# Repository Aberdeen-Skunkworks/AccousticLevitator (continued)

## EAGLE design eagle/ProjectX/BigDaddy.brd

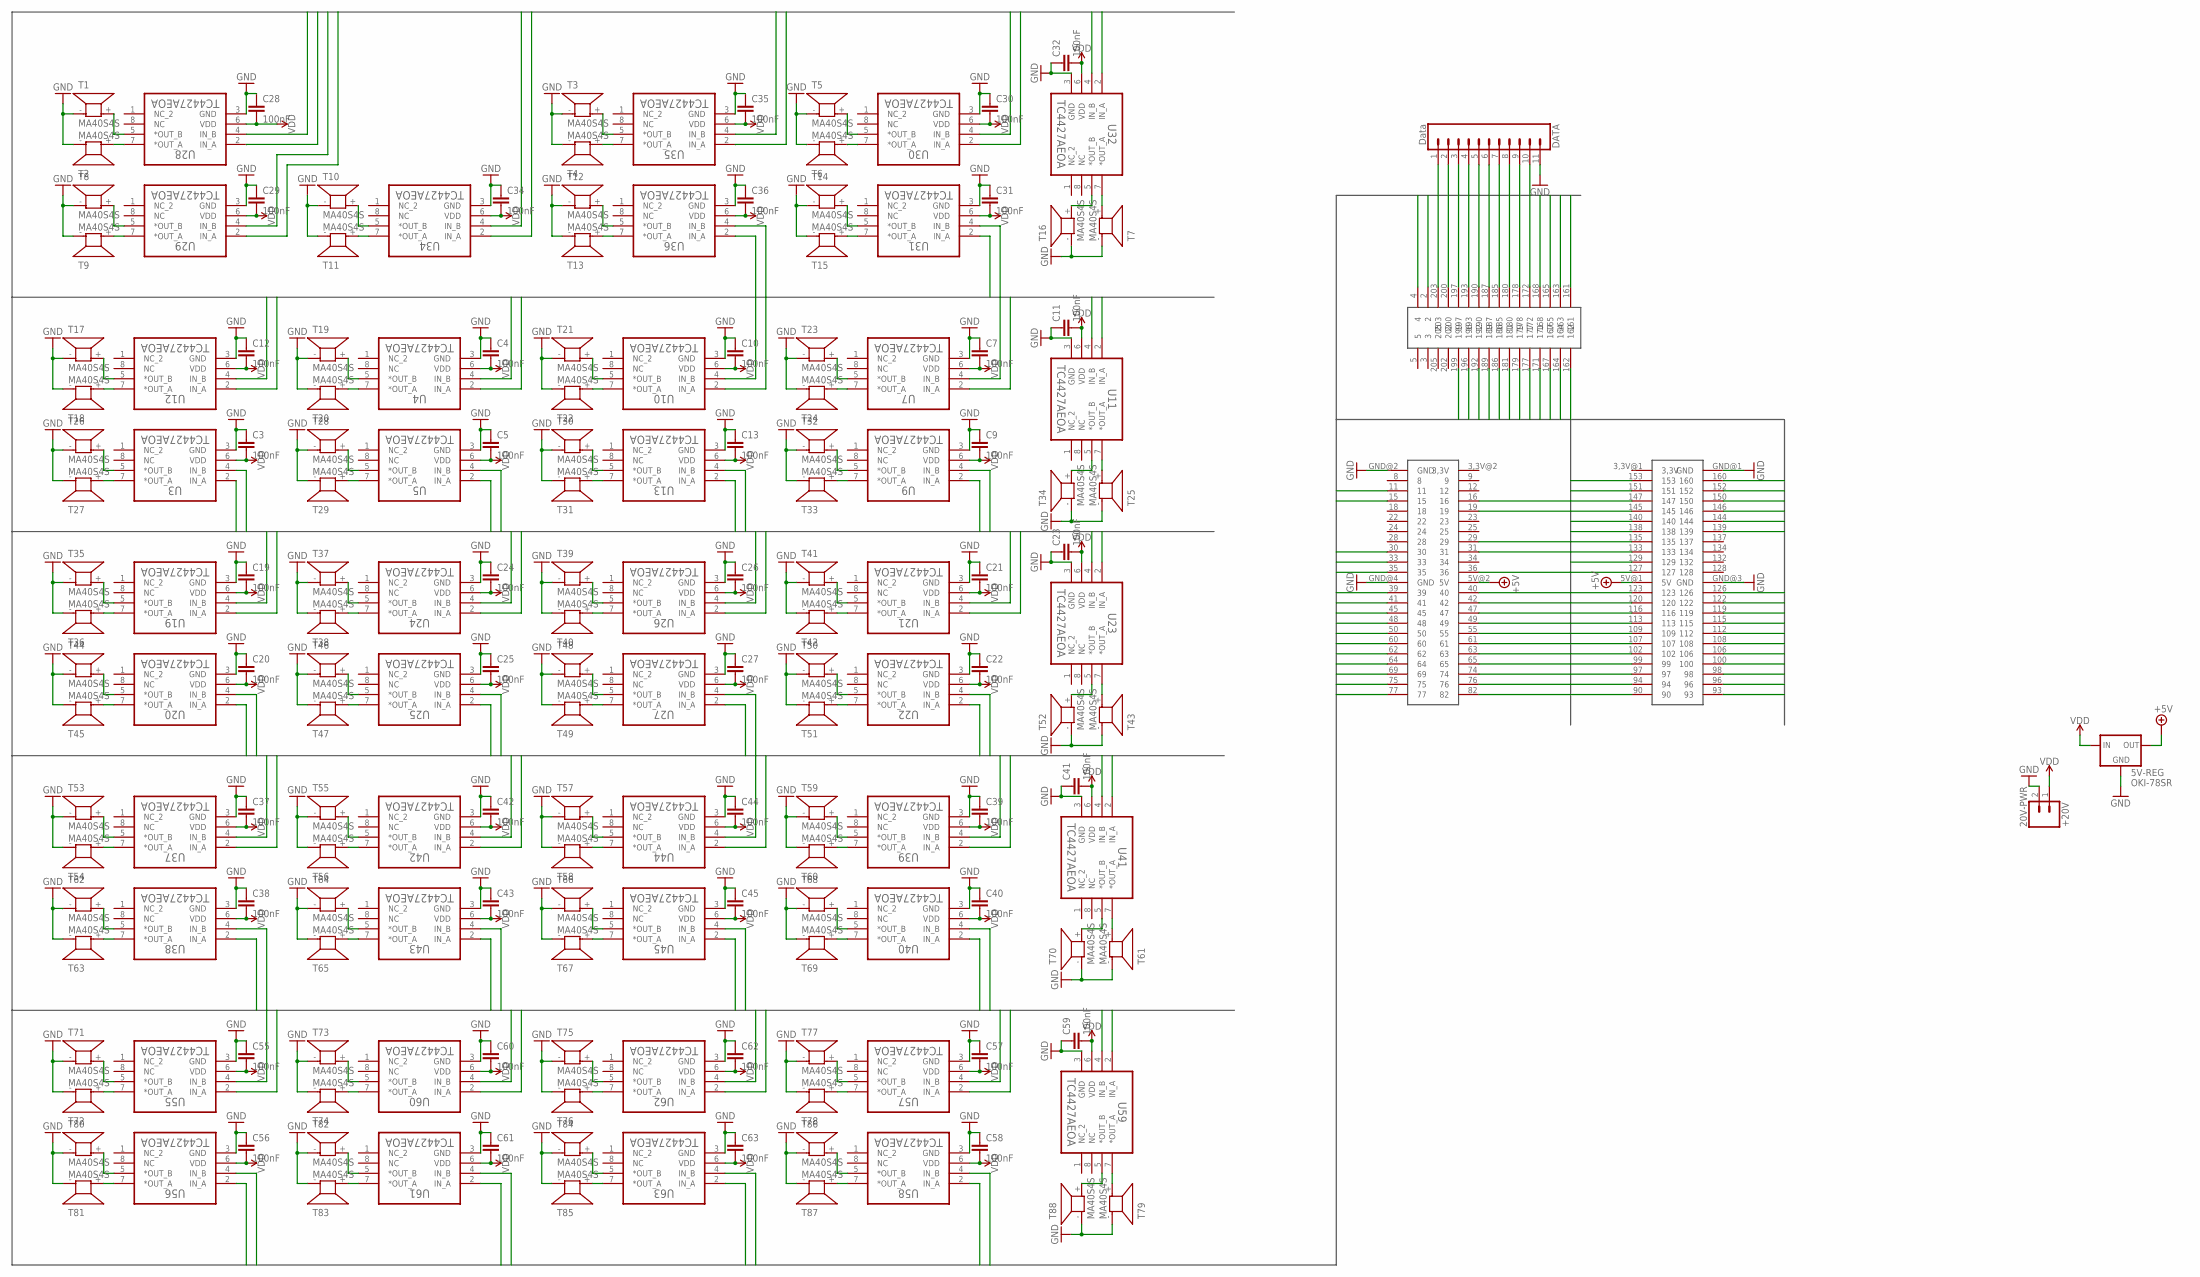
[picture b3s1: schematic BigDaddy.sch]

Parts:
5V-REG: OKI-78SR; OKI-78SR-HORIZ
20V-PWR: +20V; 1X02_LOCK_LONGPADS
C3, C4, C5, C7, C9, C10, C11, C12, C13, C19, C20, C21, C22, C23, C24, C25, C26, C27, C28, C29, C30, C31, C32, C34, C35, C36, C37, C38, C39, C40, C41, C42, C43, C44, C45, C55, C56, C57, C58, C59, C60, C61, C62, C63: 100nF; C0805
DATA: Data; 1X11
DIP1: CORE3S500ESMT; CORE3S500E-SMT
T1, T2, T3, T4, T5, T6, T7, T8, T9, T10, T11, T12, T13, T14, T15, T16, T17, T18, T19, T20, T21, T22, T23, T24, T25, T26, T27, T28, T29, T30, T31, T32, T33, T34, T35, T36, T37, T38, T39, T40, T41, T42, T43, T44, T45, T46, T47, T48, T49, T50, T51, T52, T53, T54, T55, T56, T57, T58, T59, T60, T61, T62, T63, T64, T65, T66, T67, T68, T69, T70, T71, T72, T73, T74, T75, T76, T77, T78, T79, T80, T81, T82, T83, T84, T85, T86, T87, T88: MA40S4S; MA40
U3, U4, U5, U7, U9, U10, U11, U12, U13, U19, U20, U21, U22, U23, U24, U25, U26, U27, U28, U29, U30, U31, U32, U34, U35, U36, U37, U38, U39, U40, U41, U42, U43, U44, U45, U55, U56, U57, U58, U59, U60, U61, U62, U63: TC4427AEOA; SOIC127P600X175-8N

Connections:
1: DIP1.2, U28.4 (IN_B)
2: DIP1.4, U28.2 (IN_A)
3: DIP1.165, U35.4 (IN_B)
4: DIP1.168, U35.2 (IN_A)
5: DIP1.163, U30.4 (IN_B)
6: DIP1.161, U30.2 (IN_A)
7: DIP1.162, U32.2 (IN_A)
8: DIP1.196, U29.4 (IN_B)
9: DIP1.199, U29.2 (IN_A)
10: DIP1.192, U34.4 (IN_B)
11: DIP1.189, U34.2 (IN_A)
12: DIP1.177, U36.4 (IN_B)
13: DIP1.179, U36.2 (IN_A)
14: DIP1.171, U31.4 (IN_B)
15: DIP1.167, U31.2 (IN_A)
16: DIP1.164, U32.4 (IN_B)
17: DIP1.11, U12.4 (IN_B)
18: DIP1.15, U12.2 (IN_A)
19: DIP1.19, U4.4 (IN_B)
20: DIP1.16, U4.2 (IN_A)
21: DIP1.186, U10.4 (IN_B)
22: DIP1.181, U10.2 (IN_A)
23: DIP1.152, U7.4 (IN_B)
24: DIP1.160, U7.2 (IN_A)
25: DIP1.150, U11.2 (IN_A)
26: DIP1.30, U3.4 (IN_B)
27: DIP1.33, U3.2 (IN_A)
28: DIP1.31, U5.4 (IN_B)
29: DIP1.29, U5.2 (IN_A)
30: DIP1.153, U13.4 (IN_B)
31: DIP1.151, U13.2 (IN_A)
32: DIP1.139, U9.4 (IN_B)
33: DIP1.144, U9.2 (IN_A)
34: DIP1.146, U11.4 (IN_B)
35: DIP1.35, U19.4 (IN_B)
36: DIP1.39, U19.2 (IN_A)
37: DIP1.40, U24.4 (IN_B)
38: DIP1.36, U24.2 (IN_A)
39: DIP1.147, U26.4 (IN_B)
40: DIP1.145, U26.2 (IN_A)
41: DIP1.122, U21.4 (IN_B)
42: DIP1.126, U21.2 (IN_A)
43: DIP1.119, U23.2 (IN_A)
44: DIP1.41, U20.4 (IN_B)
45: DIP1.45, U20.2 (IN_A)
46: DIP1.47, U25.4 (IN_B)
47: DIP1.42, U25.2 (IN_A)
48: DIP1.140, U27.4 (IN_B)
49: DIP1.138, U27.2 (IN_A)
50: DIP1.108, U22.4 (IN_B)
51: DIP1.112, U22.2 (IN_A)
52: DIP1.115, U23.4 (IN_B)
53: DIP1.48, U37.4 (IN_B)
54: DIP1.50, U37.2 (IN_A)
55: DIP1.55, U42.4 (IN_B)
56: DIP1.49, U42.2 (IN_A)
57: DIP1.135, U44.4 (IN_B)
58: DIP1.133, U44.2 (IN_A)
59: DIP1.100, U39.4 (IN_B)
60: DIP1.106, U39.2 (IN_A)
61: DIP1.98, U41.2 (IN_A)
62: DIP1.77, U38.4 (IN_B)
63: DIP1.75, U38.2 (IN_A)
64: DIP1.63, U43.4 (IN_B)
65: DIP1.61, U43.2 (IN_A)
66: DIP1.129, U45.4 (IN_B)
67: DIP1.127, U45.2 (IN_A)
68: DIP1.109, U40.4 (IN_B)
69: DIP1.93, U40.2 (IN_A)
70: DIP1.96, U41.4 (IN_B)
71: DIP1.69, U55.4 (IN_B)
72: DIP1.64, U55.2 (IN_A)
73: DIP1.74, U60.4 (IN_B)
74: DIP1.65, U60.2 (IN_A)
75: DIP1.123, U62.4 (IN_B)
76: DIP1.120, U62.2 (IN_A)
77: DIP1.102, U57.4 (IN_B)
78: DIP1.107, U57.2 (IN_A)
79: DIP1.99, U59.2 (IN_A)
80: DIP1.62, U56.4 (IN_B)
81: DIP1.60, U56.2 (IN_A)
82: DIP1.82, U61.4 (IN_B)
83: DIP1.76, U61.2 (IN_A)
84: DIP1.116, U63.4 (IN_B)
85: DIP1.113, U63.2 (IN_A)
86: DIP1.94, U58.4 (IN_B)
87: DIP1.90, U58.2 (IN_A)
88: DIP1.97, U59.4 (IN_B)
+5V: 5V-REG.OUT, DIP1.5V@1 (5V), DIP1.5V@2 (5V)
GND: 5V-REG.GND, 20V-PWR.2, C3.1, C4.1, C5.1, C7.1, C9.1, C10.1, C11.1, C12.1, C13.1, C19.1, C20.1, C21.1, C22.1, C23.1, C24.1, C25.1, C26.1, C27.1, C28.1, C29.1, C30.1, C31.1, C32.1, C34.1, C35.1, C36.1, C37.1, C38.1, C39.1, C40.1, C41.1, C42.1, C43.1, C44.1, C45.1, C55.1, C56.1, C57.1, C58.1, C59.1, C60.1, C61.1, C62.1, C63.1, DATA.11, DIP1.GND@1 (GND), DIP1.GND@2 (GND), DIP1.GND@3 (GND), DIP1.GND@4 (GND), T1.- (1), T2.- (1), T3.- (1), T4.- (1), T5.- (1), T6.- (1), T7.- (1), T8.- (1), T9.- (1), T10.- (1), T11.- (1), T12.- (1), T13.- (1), T14.- (1), T15.- (1), T16.- (1), T17.- (1), T18.- (1), T19.- (1), T20.- (1), T21.- (1), T22.- (1), T23.- (1), T24.- (1), T25.- (1), T26.- (1), T27.- (1), T28.- (1), T29.- (1), T30.- (1), T31.- (1), T32.- (1), T33.- (1), T34.- (1), T35.- (1), T36.- (1), T37.- (1), T38.- (1), T39.- (1), T40.- (1), T41.- (1), T42.- (1), T43.- (1), T44.- (1), T45.- (1), T46.- (1), T47.- (1), T48.- (1), T49.- (1), T50.- (1), T51.- (1), T52.- (1), T53.- (1), T54.- (1), T55.- (1), T56.- (1), T57.- (1), T58.- (1), T59.- (1), T60.- (1), T61.- (1), T62.- (1), T63.- (1), T64.- (1), T65.- (1), T66.- (1), T67.- (1), T68.- (1), T69.- (1), T70.- (1), T71.- (1), T72.- (1), T73.- (1), T74.- (1), T75.- (1), T76.- (1), T77.- (1), T78.- (1), T79.- (1), T80.- (1), T81.- (1), T82.- (1), T83.- (1), T84.- (1), T85.- (1), T86.- (1), T87.- (1), T88.- (1), U3.3 (GND), U4.3 (GND), U5.3 (GND), U7.3 (GND), U9.3 (GND), U10.3 (GND), U11.3 (GND), U12.3 (GND), U13.3 (GND), U19.3 (GND), U20.3 (GND), U21.3 (GND), U22.3 (GND), U23.3 (GND), U24.3 (GND), U25.3 (GND), U26.3 (GND), U27.3 (GND), U28.3 (GND), U29.3 (GND), U30.3 (GND), U31.3 (GND), U32.3 (GND), U34.3 (GND), U35.3 (GND), U36.3 (GND), U37.3 (GND), U38.3 (GND), U39.3 (GND), U40.3 (GND), U41.3 (GND), U42.3 (GND), U43.3 (GND), U44.3 (GND), U45.3 (GND), U55.3 (GND), U56.3 (GND), U57.3 (GND), U58.3 (GND), U59.3 (GND), U60.3 (GND), U61.3 (GND), U62.3 (GND), U63.3 (GND)
unnamed: DATA.1, DIP1.203
unnamed: DATA.2, DIP1.200
unnamed: DATA.3, DIP1.197
unnamed: DATA.4, DIP1.193
unnamed: T27.+ (2), U3.7 (*OUT_A)
unnamed: T26.+ (2), U3.5 (*OUT_B)
unnamed: T20.+ (2), U4.7 (*OUT_A)
unnamed: T19.+ (2), U4.5 (*OUT_B)
unnamed: T29.+ (2), U5.7 (*OUT_A)
unnamed: T28.+ (2), U5.5 (*OUT_B)
unnamed: DATA.5, DIP1.190
unnamed: DATA.6, DIP1.187
unnamed: T24.+ (2), U7.7 (*OUT_A)
unnamed: T23.+ (2), U7.5 (*OUT_B)
unnamed: DATA.7, DIP1.185
unnamed: DATA.8, DIP1.180
unnamed: T33.+ (2), U9.7 (*OUT_A)
unnamed: T32.+ (2), U9.5 (*OUT_B)
unnamed: T22.+ (2), U10.7 (*OUT_A)
unnamed: T21.+ (2), U10.5 (*OUT_B)
unnamed: T25.+ (2), U11.7 (*OUT_A)
unnamed: T34.+ (2), U11.5 (*OUT_B)
unnamed: T18.+ (2), U12.7 (*OUT_A)
unnamed: T17.+ (2), U12.5 (*OUT_B)
unnamed: T31.+ (2), U13.7 (*OUT_A)
unnamed: T30.+ (2), U13.5 (*OUT_B)
unnamed: DATA.9, DIP1.178
unnamed: DATA.10, DIP1.172
unnamed: T36.+ (2), U19.7 (*OUT_A)
unnamed: T35.+ (2), U19.5 (*OUT_B)
unnamed: T45.+ (2), U20.7 (*OUT_A)
unnamed: T44.+ (2), U20.5 (*OUT_B)
unnamed: T42.+ (2), U21.7 (*OUT_A)
unnamed: T41.+ (2), U21.5 (*OUT_B)
unnamed: T51.+ (2), U22.7 (*OUT_A)
unnamed: T50.+ (2), U22.5 (*OUT_B)
unnamed: T43.+ (2), U23.7 (*OUT_A)
unnamed: T52.+ (2), U23.5 (*OUT_B)
unnamed: T38.+ (2), U24.7 (*OUT_A)
unnamed: T37.+ (2), U24.5 (*OUT_B)
unnamed: T47.+ (2), U25.7 (*OUT_A)
unnamed: T46.+ (2), U25.5 (*OUT_B)
unnamed: T40.+ (2), U26.7 (*OUT_A)
unnamed: T39.+ (2), U26.5 (*OUT_B)
unnamed: T49.+ (2), U27.7 (*OUT_A)
unnamed: T48.+ (2), U27.5 (*OUT_B)
unnamed: T2.+ (2), U28.7 (*OUT_A)
unnamed: T1.+ (2), U28.5 (*OUT_B)
unnamed: T9.+ (2), U29.7 (*OUT_A)
unnamed: T8.+ (2), U29.5 (*OUT_B)
unnamed: T6.+ (2), U30.7 (*OUT_A)
unnamed: T5.+ (2), U30.5 (*OUT_B)
unnamed: T15.+ (2), U31.7 (*OUT_A)
unnamed: T14.+ (2), U31.5 (*OUT_B)
unnamed: T7.+ (2), U32.7 (*OUT_A)
unnamed: T16.+ (2), U32.5 (*OUT_B)
unnamed: T11.+ (2), U34.7 (*OUT_A)
unnamed: T10.+ (2), U34.5 (*OUT_B)
unnamed: T4.+ (2), U35.7 (*OUT_A)
unnamed: T3.+ (2), U35.5 (*OUT_B)
unnamed: T13.+ (2), U36.7 (*OUT_A)
unnamed: T12.+ (2), U36.5 (*OUT_B)
unnamed: T54.+ (2), U37.7 (*OUT_A)
unnamed: T53.+ (2), U37.5 (*OUT_B)
unnamed: T63.+ (2), U38.7 (*OUT_A)
unnamed: T62.+ (2), U38.5 (*OUT_B)
unnamed: T60.+ (2), U39.7 (*OUT_A)
unnamed: T59.+ (2), U39.5 (*OUT_B)
unnamed: T69.+ (2), U40.7 (*OUT_A)
unnamed: T68.+ (2), U40.5 (*OUT_B)
unnamed: T61.+ (2), U41.7 (*OUT_A)
unnamed: T70.+ (2), U41.5 (*OUT_B)
unnamed: T56.+ (2), U42.7 (*OUT_A)
unnamed: T55.+ (2), U42.5 (*OUT_B)
unnamed: T65.+ (2), U43.7 (*OUT_A)
unnamed: T64.+ (2), U43.5 (*OUT_B)
unnamed: T58.+ (2), U44.7 (*OUT_A)
unnamed: T57.+ (2), U44.5 (*OUT_B)
unnamed: T67.+ (2), U45.7 (*OUT_A)
unnamed: T66.+ (2), U45.5 (*OUT_B)
unnamed: T72.+ (2), U55.7 (*OUT_A)
unnamed: T71.+ (2), U55.5 (*OUT_B)
unnamed: T81.+ (2), U56.7 (*OUT_A)
unnamed: T80.+ (2), U56.5 (*OUT_B)
unnamed: T78.+ (2), U57.7 (*OUT_A)
unnamed: T77.+ (2), U57.5 (*OUT_B)
unnamed: T87.+ (2), U58.7 (*OUT_A)
unnamed: T86.+ (2), U58.5 (*OUT_B)
unnamed: T79.+ (2), U59.7 (*OUT_A)
unnamed: T88.+ (2), U59.5 (*OUT_B)
unnamed: T74.+ (2), U60.7 (*OUT_A)
unnamed: T73.+ (2), U60.5 (*OUT_B)
unnamed: T83.+ (2), U61.7 (*OUT_A)
unnamed: T82.+ (2), U61.5 (*OUT_B)
unnamed: T76.+ (2), U62.7 (*OUT_A)
unnamed: T75.+ (2), U62.5 (*OUT_B)
unnamed: T85.+ (2), U63.7 (*OUT_A)
unnamed: T84.+ (2), U63.5 (*OUT_B)
VDD: 5V-REG.IN, 20V-PWR.1, C3.2, C4.2, C5.2, C7.2, C9.2, C10.2, C11.2, C12.2, C13.2, C19.2, C20.2, C21.2, C22.2, C23.2, C24.2, C25.2, C26.2, C27.2, C28.2, C29.2, C30.2, C31.2, C32.2, C34.2, C35.2, C36.2, C37.2, C38.2, C39.2, C40.2, C41.2, C42.2, C43.2, C44.2, C45.2, C55.2, C56.2, C57.2, C58.2, C59.2, C60.2, C61.2, C62.2, C63.2, U3.6 (VDD), U4.6 (VDD), U5.6 (VDD), U7.6 (VDD), U9.6 (VDD), U10.6 (VDD), U11.6 (VDD), U12.6 (VDD), U13.6 (VDD), U19.6 (VDD), U20.6 (VDD), U21.6 (VDD), U22.6 (VDD), U23.6 (VDD), U24.6 (VDD), U25.6 (VDD), U26.6 (VDD), U27.6 (VDD), U28.6 (VDD), U29.6 (VDD), U30.6 (VDD), U31.6 (VDD), U32.6 (VDD), U34.6 (VDD), U35.6 (VDD), U36.6 (VDD), U37.6 (VDD), U38.6 (VDD), U39.6 (VDD), U40.6 (VDD), U41.6 (VDD), U42.6 (VDD), U43.6 (VDD), U44.6 (VDD), U45.6 (VDD), U55.6 (VDD), U56.6 (VDD), U57.6 (VDD), U58.6 (VDD), U59.6 (VDD), U60.6 (VDD), U61.6 (VDD), U62.6 (VDD), U63.6 (VDD)

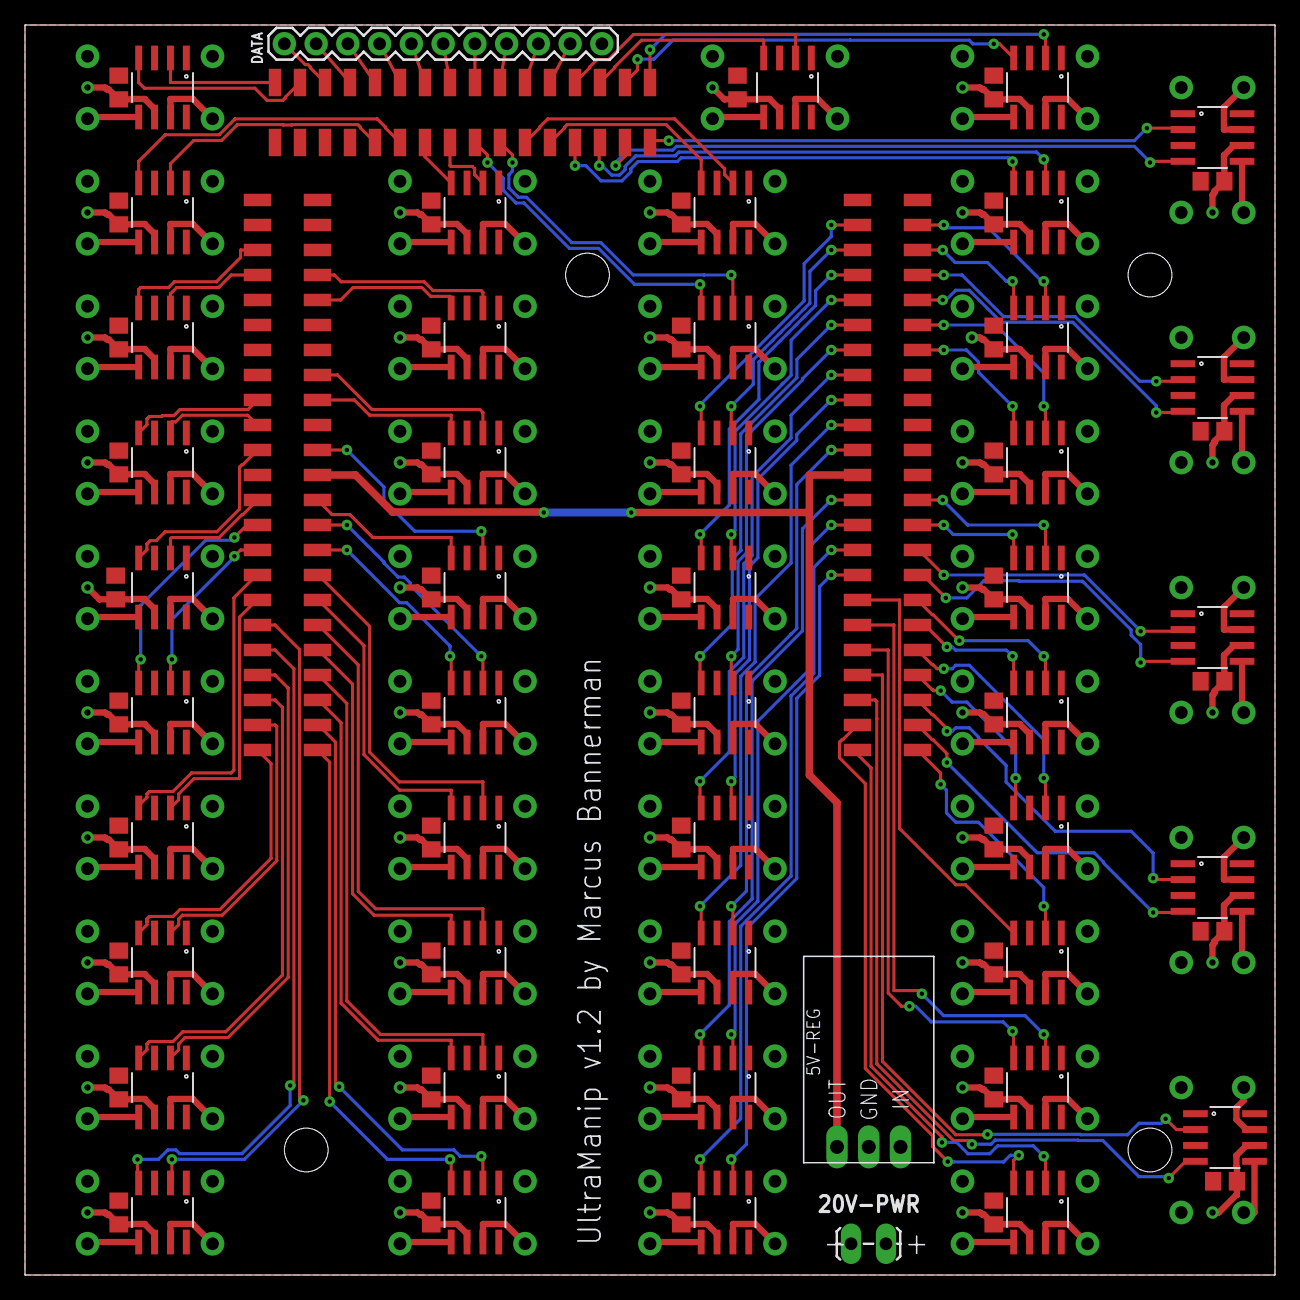
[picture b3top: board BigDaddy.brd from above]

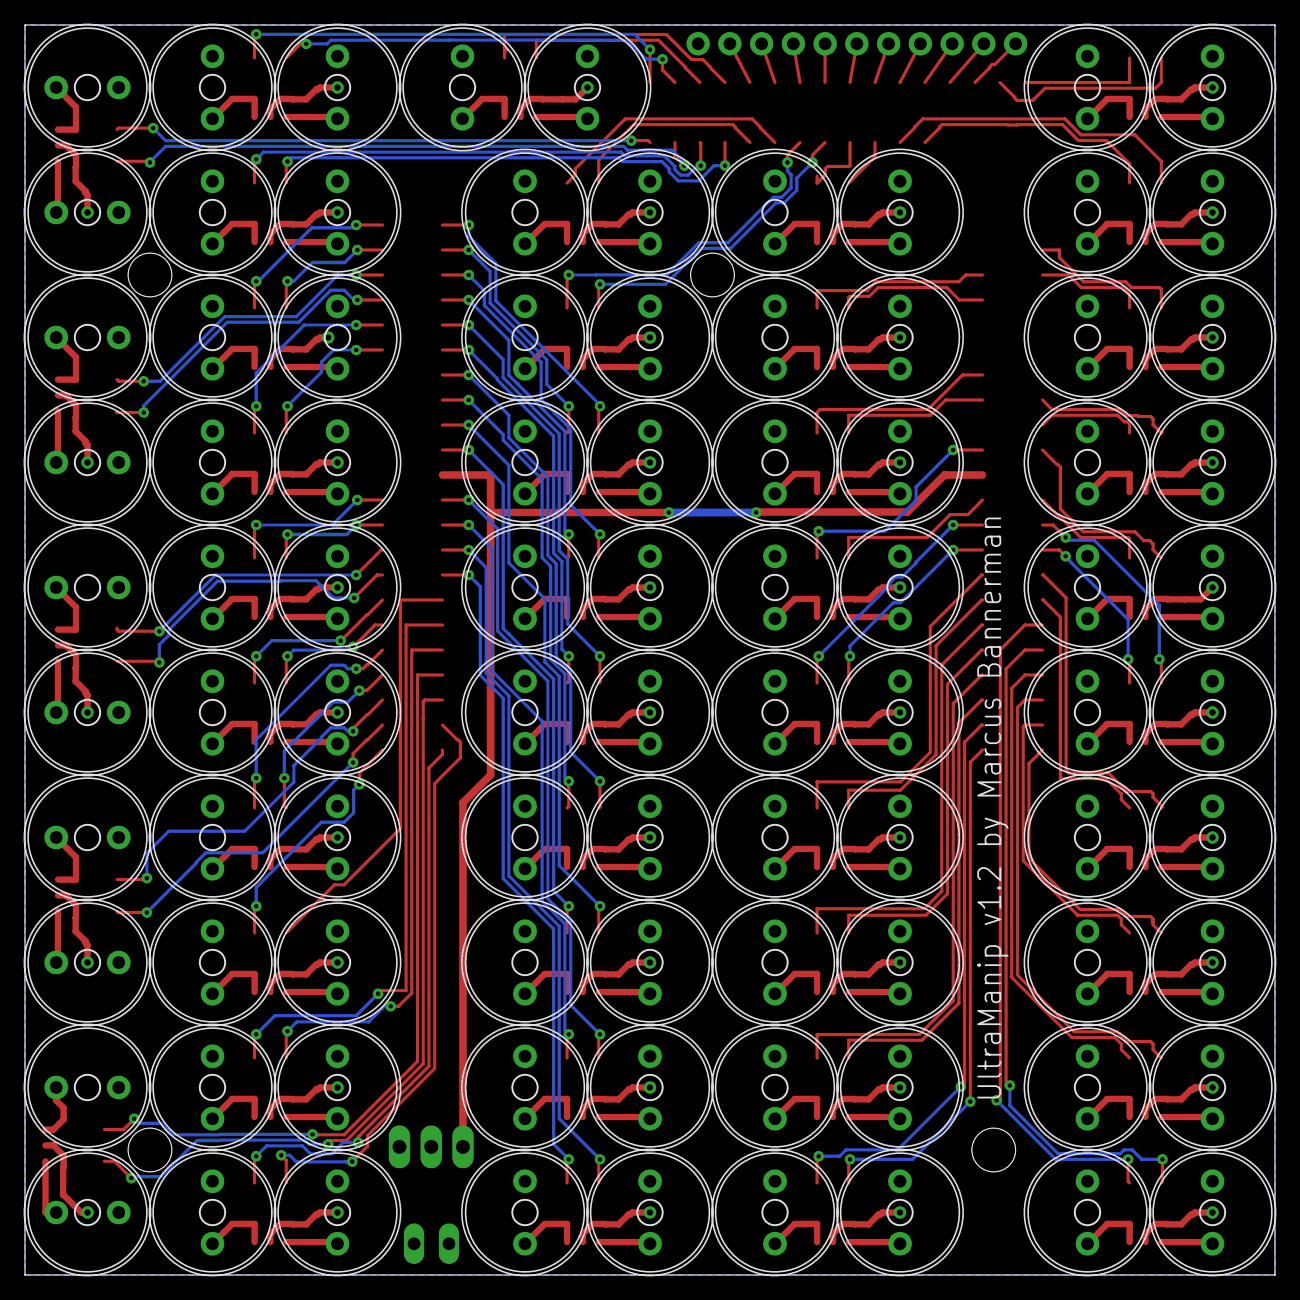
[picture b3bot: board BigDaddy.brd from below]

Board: 2 copper layers, 100.0 x 100.0 mm, 180 parts (88 on the bottom side), 189 nets.

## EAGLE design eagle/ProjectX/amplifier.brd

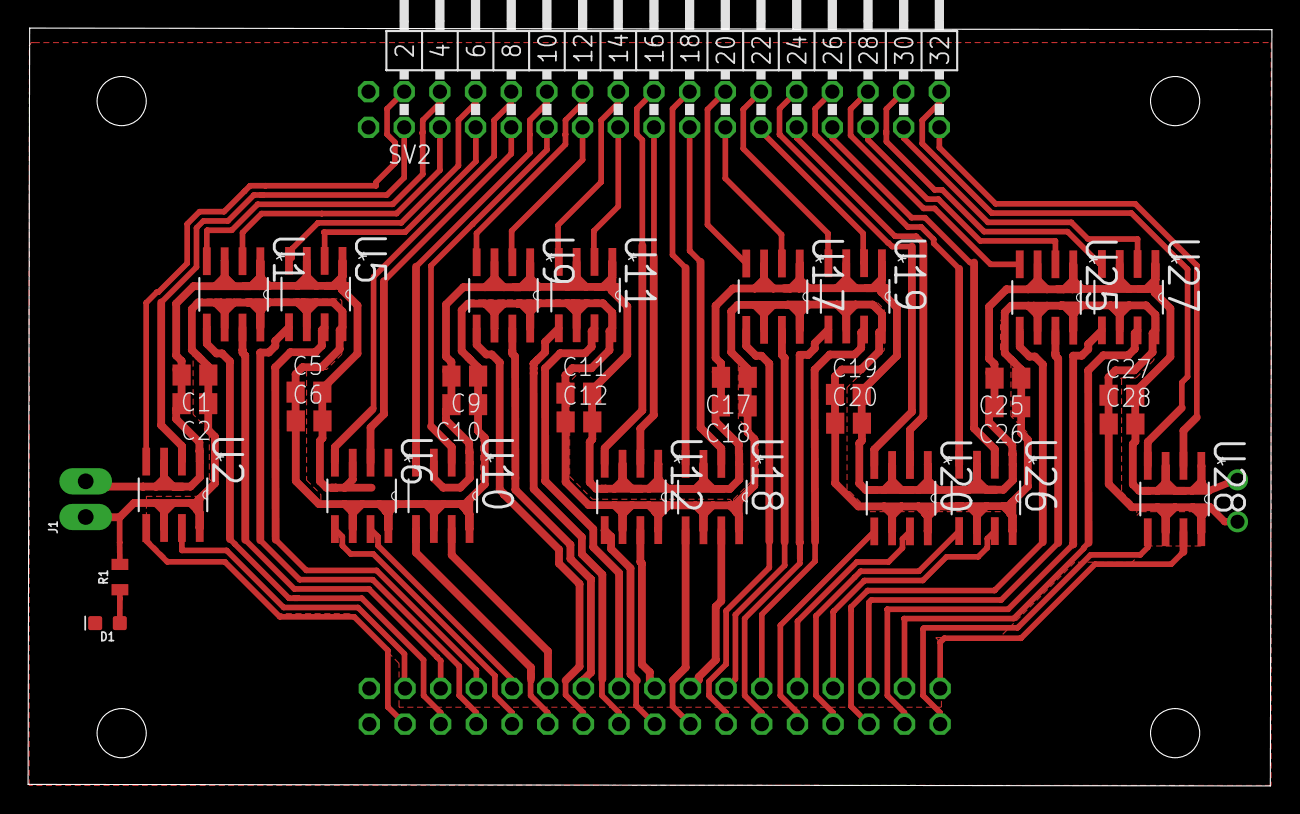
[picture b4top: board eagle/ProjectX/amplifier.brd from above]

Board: 2 copper layers, 88.6 x 54.0 mm, 37 parts (1 on the bottom side), 67 nets.

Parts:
C1, C5, C9, C11, C17, C19, C25, C27: 4.7uF; C0805
C2, C6, C10, C12, C18, C20, C26, C28: 100nF; C0805
D1: LED-0603
J1: 1X02_LONGPADS
R1: 1k; 0805
SV1, SV2: MA20-2W
U1, U2, U5, U6, U9, U10, U11, U12, U17, U18, U19, U20, U25, U26, U27, U28: TC4427COA; SOIC127P600X175-8N

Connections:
GND: C1.2, C2.2, C5.2, C6.2, C9.2, C10.2, C11.2, C12.2, C17.2, C18.2, C19.2, C20.2, C25.2, C26.2, C27.2, C28.2, D1.C, J1.2, SV1.GND, SV1.GND+1, SV2.GND, SV2.GND+1, U1.1, U1.3, U2.1, U2.3, U5.1, U5.3, U6.1, U6.3, U9.1, U9.3, U10.1, U10.3, U11.1, U11.3, U12.1, U12.3, U17.1, U17.3, U18.1, U18.3, U19.1, U19.3, U20.1, U20.3, U25.1, U25.3, U26.1, U26.3, U27.1, U27.3, U28.1, U28.3
unnamed: SV2.2, U2.4
unnamed: SV1.2, U2.5
unnamed: SV1.4, U1.5
unnamed: SV2.4, U1.4
unnamed: SV2.3, U1.2
unnamed: SV2.1, U2.2
unnamed: SV1.16, U12.5
unnamed: SV1.24, U20.5
unnamed: SV1.8, U6.5
unnamed: SV1.1, U2.7
unnamed: SV1.3, U1.7
unnamed: SV1.7, U6.7
unnamed: SV1.10, U10.5
unnamed: SV1.9, U10.7
unnamed: SV1.11, U9.7
unnamed: SV1.23, U20.7
unnamed: SV2.6, U5.4
unnamed: SV2.5, U5.2
unnamed: SV2.8, U6.4
unnamed: D1.A, R1.1
unnamed: SV2.7, U6.2
unnamed: SV1.5, U5.7
unnamed: SV1.6, U5.5
unnamed: SV1.15, U12.7
unnamed: SV1.12, U9.5
unnamed: SV2.12, U9.4
unnamed: SV2.11, U9.2
unnamed: SV2.10, U10.4
unnamed: SV2.9, U10.2
unnamed: SV2.14, U11.4
unnamed: SV2.13, U11.2
unnamed: SV2.16, U12.4
unnamed: SV2.15, U12.2
unnamed: SV1.13, U11.7
unnamed: SV1.14, U11.5
unnamed: SV2.20, U17.4
unnamed: SV2.19, U17.2
unnamed: SV2.18, U18.4
unnamed: SV1.17, U18.7
unnamed: SV1.18, U18.5
unnamed: SV2.17, U18.2
unnamed: SV1.19, U17.7
unnamed: SV1.20, U17.5
unnamed: SV2.22, U19.4
unnamed: SV2.21, U19.2
unnamed: SV2.24, U20.4
unnamed: SV2.23, U20.2
unnamed: SV1.21, U19.7
unnamed: SV1.22, U19.5
unnamed: SV2.28, U25.4
unnamed: SV2.27, U25.2
unnamed: SV2.26, U26.4
unnamed: SV1.25, U26.7
unnamed: SV1.26, U26.5
unnamed: SV2.25, U26.2
unnamed: SV1.27, U25.7
unnamed: SV1.28, U25.5
unnamed: SV2.30, U27.4
unnamed: SV2.29, U27.2
unnamed: SV2.32, U28.4
unnamed: SV1.31, U28.7
unnamed: SV1.32, U28.5
unnamed: SV2.31, U28.2
unnamed: SV1.29, U27.7
unnamed: SV1.30, U27.5
VDD: C1.1, C2.1, C5.1, C6.1, C9.1, C10.1, C11.1, C12.1, C17.1, C18.1, C19.1, C20.1, C25.1, C26.1, C27.1, C28.1, J1.1, R1.2, U1.6, U1.8, U2.6, U2.8, U5.6, U5.8, U6.6, U6.8, U9.6, U9.8, U10.6, U10.8, U11.6, U11.8, U12.6, U12.8, U17.6, U17.8, U18.6, U18.8, U19.6, U19.8, U20.6, U20.8, U25.6, U25.8, U26.6, U26.8, U27.6, U27.8, U28.6, U28.8

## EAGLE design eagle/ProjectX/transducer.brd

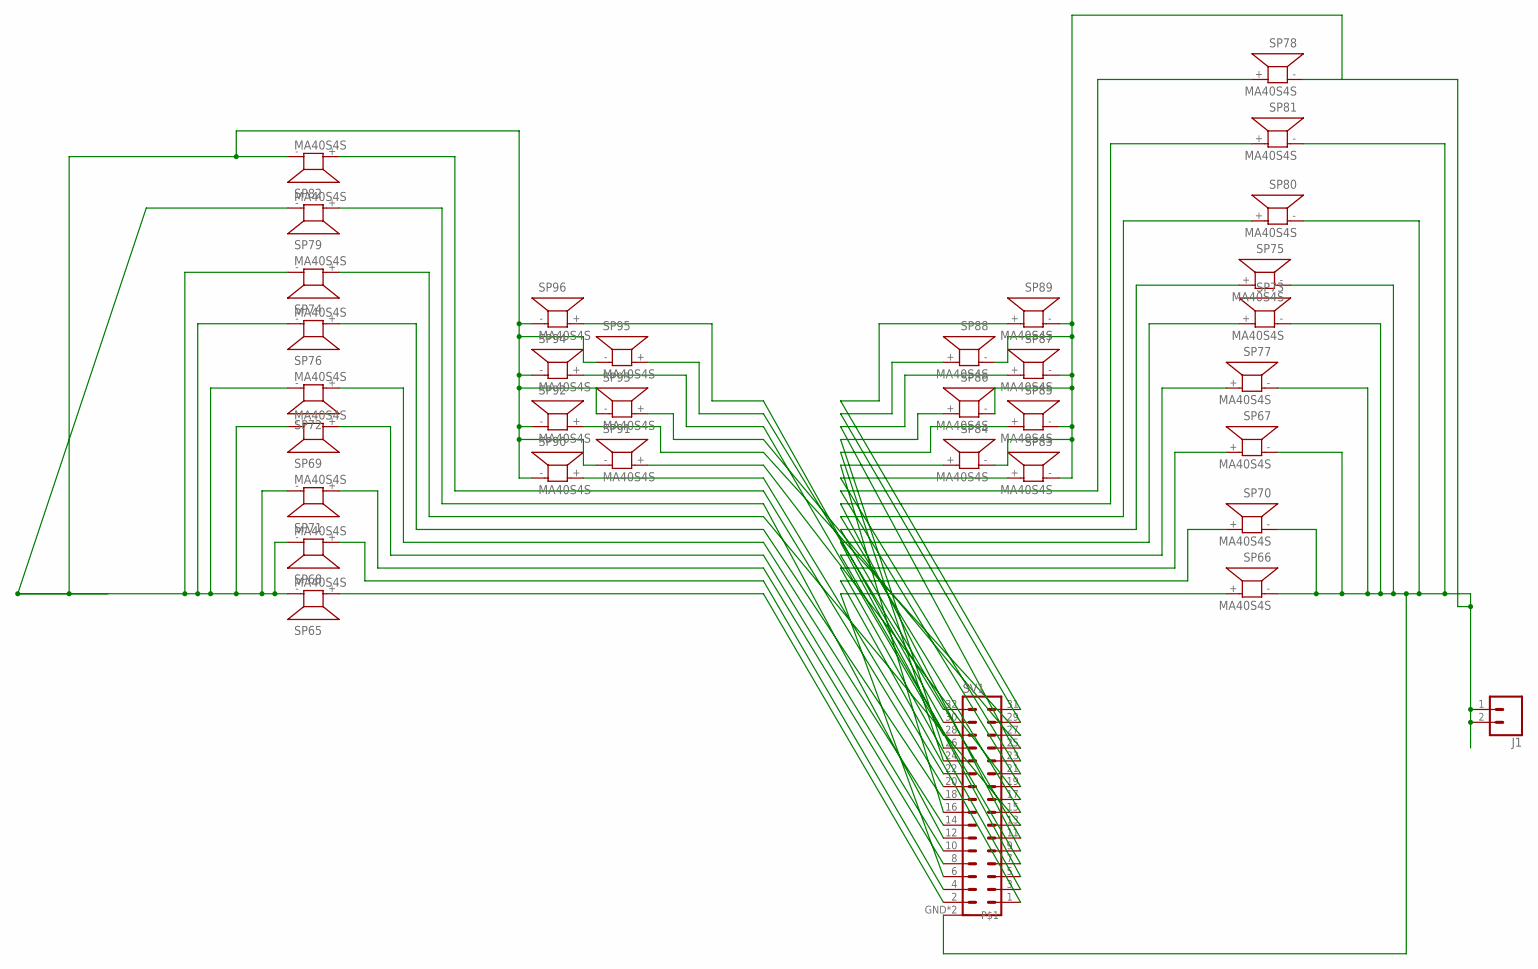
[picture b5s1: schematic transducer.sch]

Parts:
J1: CONN_02PTH3; 1X02_LONGPADS
SP65, SP66, SP67, SP68, SP69, SP70, SP71, SP72, SP73, SP74, SP75, SP76, SP77, SP78, SP79, SP80, SP81, SP82, SP83, SP84, SP85, SP86, SP87, SP88, SP89, SP90, SP91, SP92, SP93, SP94, SP95, SP96: MA40S4S; MA40
SV1: MA20-2W

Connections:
GND: J1.1, J1.2, SP65.- (1), SP66.- (1), SP67.- (1), SP68.- (1), SP69.- (1), SP70.- (1), SP71.- (1), SP72.- (1), SP73.- (1), SP74.- (1), SP75.- (1), SP76.- (1), SP77.- (1), SP78.- (1), SP79.- (1), SP80.- (1), SP81.- (1), SP82.- (1), SP83.- (1), SP84.- (1), SP85.- (1), SP86.- (1), SP87.- (1), SP88.- (1), SP89.- (1), SP90.- (1), SP91.- (1), SP92.- (1), SP93.- (1), SP94.- (1), SP95.- (1), SP96.- (1), SV1.GND, SV1.GND+1
unnamed: SP65.+ (2), SV1.2
unnamed: SP66.+ (2), SV1.6
unnamed: SP68.+ (2), SV1.4
unnamed: SP70.+ (2), SV1.1
unnamed: SP67.+ (2), SV1.3
unnamed: SP69.+ (2), SV1.10
unnamed: SP77.+ (2), SV1.7
unnamed: SP76.+ (2), SV1.18
unnamed: SP71.+ (2), SV1.8
unnamed: SP73.+ (2), SV1.5
unnamed: SP74.+ (2), SV1.13
unnamed: SP75.+ (2), SV1.11
unnamed: SP72.+ (2), SV1.14
unnamed: SP80.+ (2), SV1.15
unnamed: SP79.+ (2), SV1.12
unnamed: SP81.+ (2), SV1.9
unnamed: SP82.+ (2), SV1.20
unnamed: SP78.+ (2), SV1.19
unnamed: SP83.+ (2), SV1.21
unnamed: SP84.+ (2), SV1.16
unnamed: SP85.+ (2), SV1.24
unnamed: SP86.+ (2), SV1.26
unnamed: SP87.+ (2), SV1.23
unnamed: SP88.+ (2), SV1.29
unnamed: SP89.+ (2), SV1.31
unnamed: SP90.+ (2), SV1.22
unnamed: SP91.+ (2), SV1.17
unnamed: SP92.+ (2), SV1.27
unnamed: SP93.+ (2), SV1.25
unnamed: SP94.+ (2), SV1.28
unnamed: SP95.+ (2), SV1.32
unnamed: SP96.+ (2), SV1.30

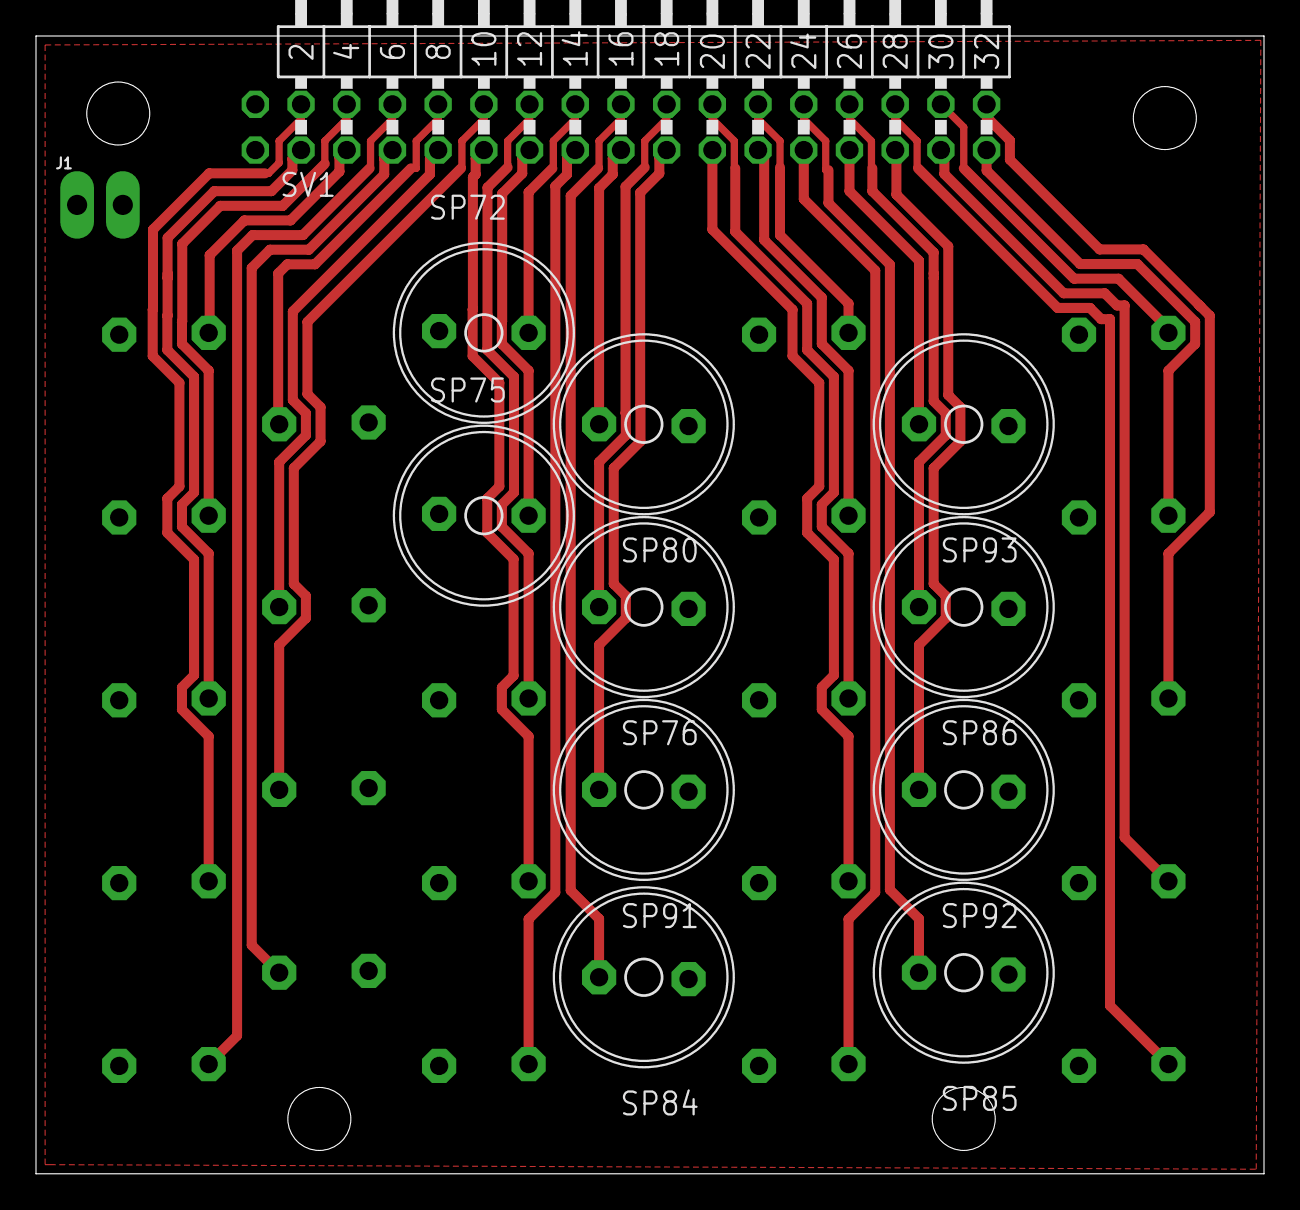
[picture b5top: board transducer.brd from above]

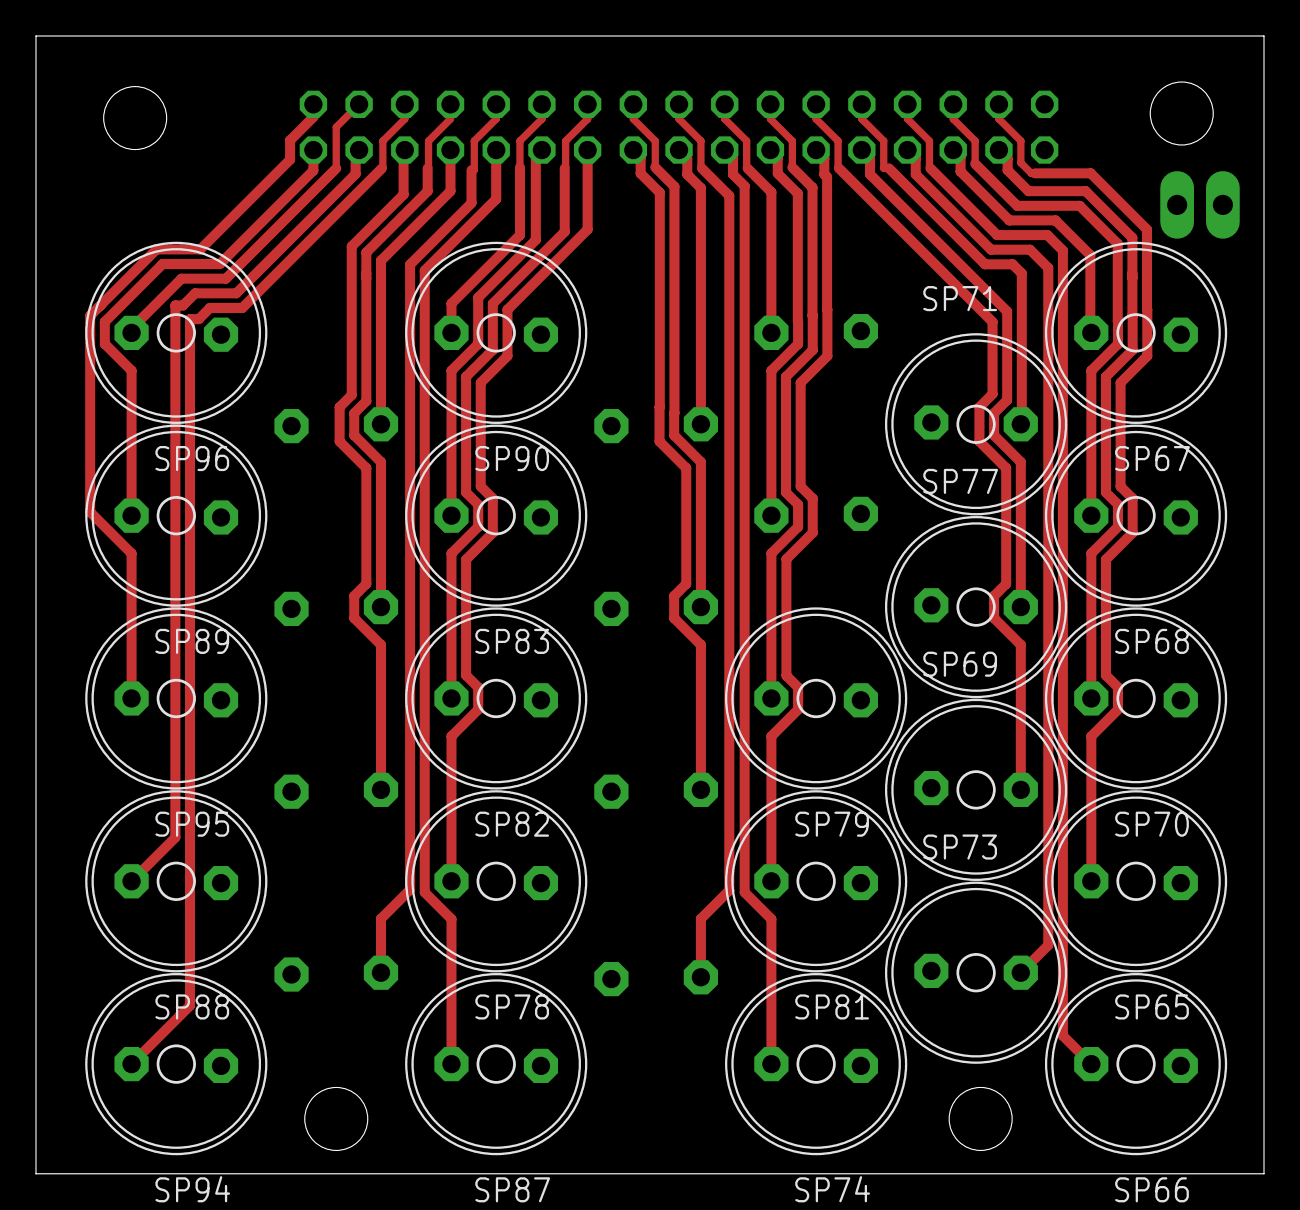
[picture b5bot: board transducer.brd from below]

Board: 2 copper layers, 68.2 x 63.2 mm, 34 parts (22 on the bottom side), 33 nets.

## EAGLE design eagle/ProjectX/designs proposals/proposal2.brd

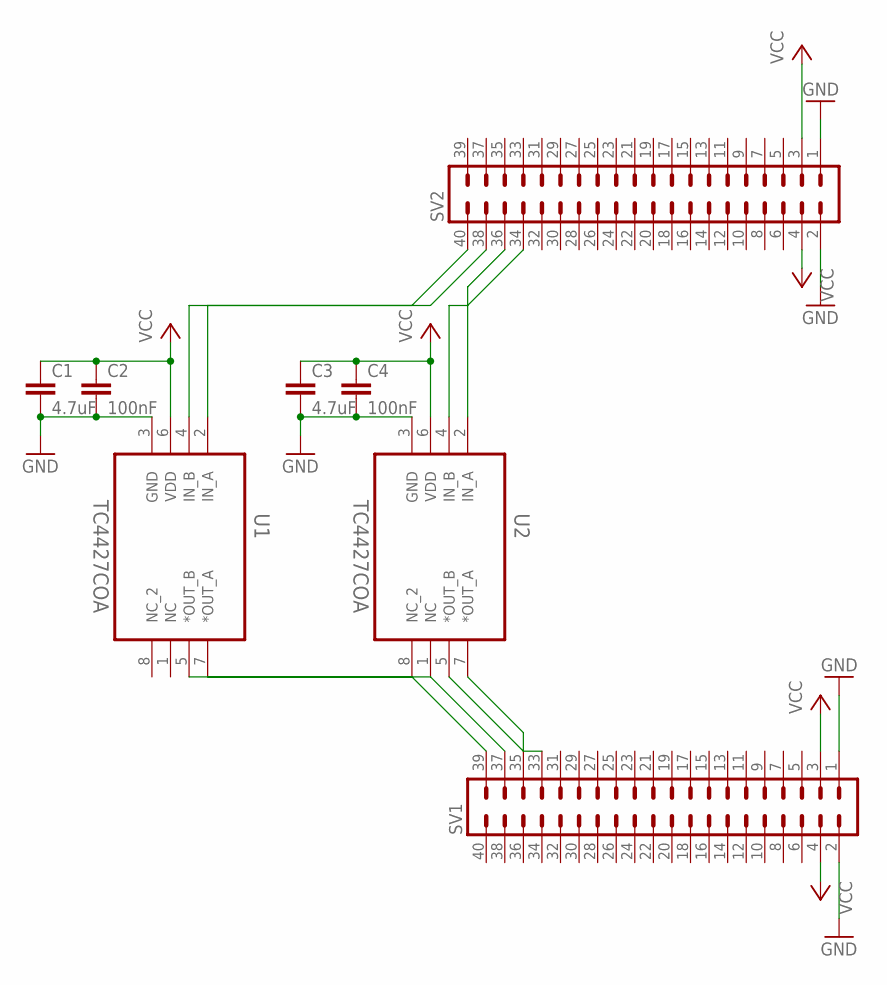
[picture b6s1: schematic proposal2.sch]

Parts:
C1, C3: 4.7uF; C0805
C2, C4: 100nF; C0805
SV1, SV2: MA20-2W
U1, U2: TC4427COA; SOIC127P600X175-8N

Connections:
GND: C1.2, C2.2, C3.2, C4.2, SV1.1, SV1.2, SV2.1, SV2.2, U1.3 (GND), U2.3 (GND)
unnamed: SV2.34, U2.4 (IN_B)
unnamed: SV1.39, U1.7 (*OUT_A)
unnamed: SV1.37, U1.5 (*OUT_B)
unnamed: SV2.38, U1.4 (IN_B)
unnamed: SV2.40, U1.2 (IN_A)
unnamed: SV2.36, U2.2 (IN_A)
unnamed: SV1.35, U2.7 (*OUT_A)
unnamed: SV1.33, U2.5 (*OUT_B)
VCC: C1.1, C2.1, C3.1, C4.1, SV1.3, SV1.4, SV2.3, SV2.4, U1.6 (VDD), U2.6 (VDD)

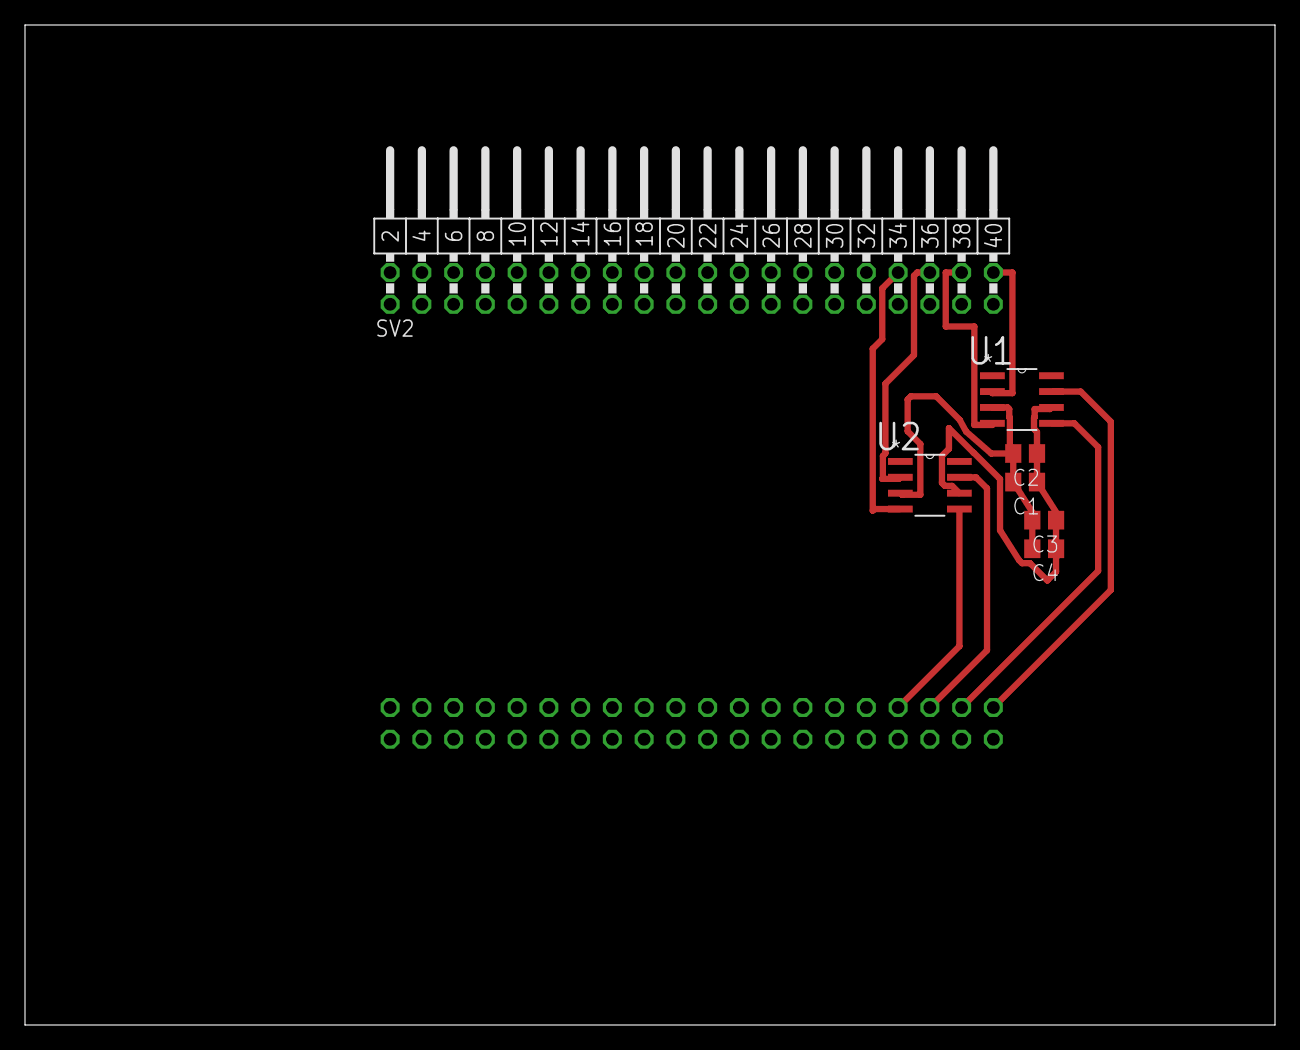
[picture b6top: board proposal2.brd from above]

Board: 2 copper layers, 100.0 x 80.0 mm, 8 parts (1 on the bottom side), 10 nets.
